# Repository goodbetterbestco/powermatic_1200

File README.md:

# Powermatic 1200 Controls Retrofit

Rev P is the current contactor-based design. Operator controls use 24 VDC; motor-power switching is in the panel enclosure. Schematic, layout and commissioning work remain open.

Backplate layout and DIN-rail/wire-duct installation are complete, as reported on 2026-10-27. All 20 mounting holes were drilled and tapped 10-24; the specified 10-24 fasteners worked well. See the [installation record](docs/WIRING_STANDARD.md#current-document-set---2026-11-09).

Modules and terminal blocks were reported placed on 2026-10-28. The 2026-10-30 saved layout places FH1 at the lower rail’s right end, after 5K, G4 and the existing end stop. Incoming phase blocks 4E/4F/4G are removed; the cable phases now terminate directly at FH1. G4 remains. The mains entry is on the right wall; the two alternate right-face motor/control holes are recorded in the enclosure drawing. Two McMaster 9357K15 gasketed plugs with hex retaining nuts cover the unused motor/control pair. Terminal labels use module number + letter, skipping I/O, with G1-G6 for grounding blocks. Jumper installation is the next assembly step.

## Active files

- [BOM](BOM_other.csv): project requirements and purchasing quantities. `BOM_jlcpcb.csv` is reserved for a separate JLCPCB BOM when needed.
- [KiCad project](kicad/powermatic_1200/powermatic_1200.kicad_pro) and [schematic](kicad/powermatic_1200/powermatic_1200.kicad_sch).

The `docs/` folder contains eight essential files:

- [Panel drawings](docs/Panel_drawings.pdf): module layout, terminal jumpers and markers, approved backpanel drilling sheet, and enclosure holes. The enclosure sheet is PDF page 6; print it at 96% for 1:1 details. The earlier BB1/BB2 busbar artwork is superseded by the six K1/K2 wire jumpers in the wiring guide.
- [Wire installation guide](docs/Wire_installation_guide.pdf): labeling, connector identification and strip settings on PDF pages 2-5, followed by the 131-row installation checklist on pages 6-8.
- [Wiring standard and reference notes](docs/WIRING_STANDARD.md): wiring policy, installation sequence, terminal numbering, signal names, preparation sources, and the two supplemental pendant-jumper records.
- [Saved wire schedule](docs/Wire_schedule.csv): 129 native wires; the printable guide also includes two supplemental pendant jumpers.
- [Wire length totals](docs/Wire_length_totals.csv).
- [Connector inventory](docs/Wire_connector_bins.csv), [installation order](docs/Wire_installation_groups.json), and [termination-code mapping](docs/Wire_termination_types.json): required inputs for Project Review Refresh.

Refresh updates the saved schedule and wire totals. Rebuild and reconcile the PDF guide after changing the native wiring; Refresh does not rebuild it. Preserve the two supplemental pendant rows recorded in the wiring standard.

## Project Review

Double-click **Project Review.app** to launch the separate [bom_review editor](https://github.com/goodbetterbestco/bom_review), installed at `~/Projects/bom_review`. **Documents** lists root CSVs plus the saved wire schedule and wire-length totals in `docs/`. **Overwrite** saves the selected document; **Save file** downloads a copy. For **Wire_schedule.csv**, **Refresh** regenerates the schedule and length totals from saved KiCad; for other documents it reloads the saved CSV. The extractor and project configuration live in `~/Projects/bom_review/adapters/powermatic_1200/`, outside this hardware repository.

`QUA` is the project requirement in pieces or feet. `PACK` is the amount per purchase unit, `ORDER` is the number of purchase units, and `COST` is the price per purchase unit. `LINE = ORDER × COST`. GBB items are on hand and keep `ORDER = 0`. The CSV is manually reviewed; the launcher does not regenerate it from KiCad.

`FLAG` and `FLAG DESCRIPTION` retain the review selection and its document-wide description in the CSV. The app displays them through the checkbox and Description controls. Use **Overwrite** to save changes; reopening or Refresh restores the saved flags. Flags indicate the purpose stated in Description and do not change purchasing quantities.

## Shared parts

Reusable symbols, footprints, models and datasheets belong in the sibling `_parts` repository. The enclosure selection is Hammond EN4SD30208GY with EP3020 backplate. Verify the saved schematic, board and physical fit independently before fabrication or procurement.

## Repository policy

See [AGENTS.md](AGENTS.md). Supporting documents belong in `docs/`; temporary tools, generated reviews and automatic backup folders are removed. Earlier scripts and reports remain available in Git history when previously committed.

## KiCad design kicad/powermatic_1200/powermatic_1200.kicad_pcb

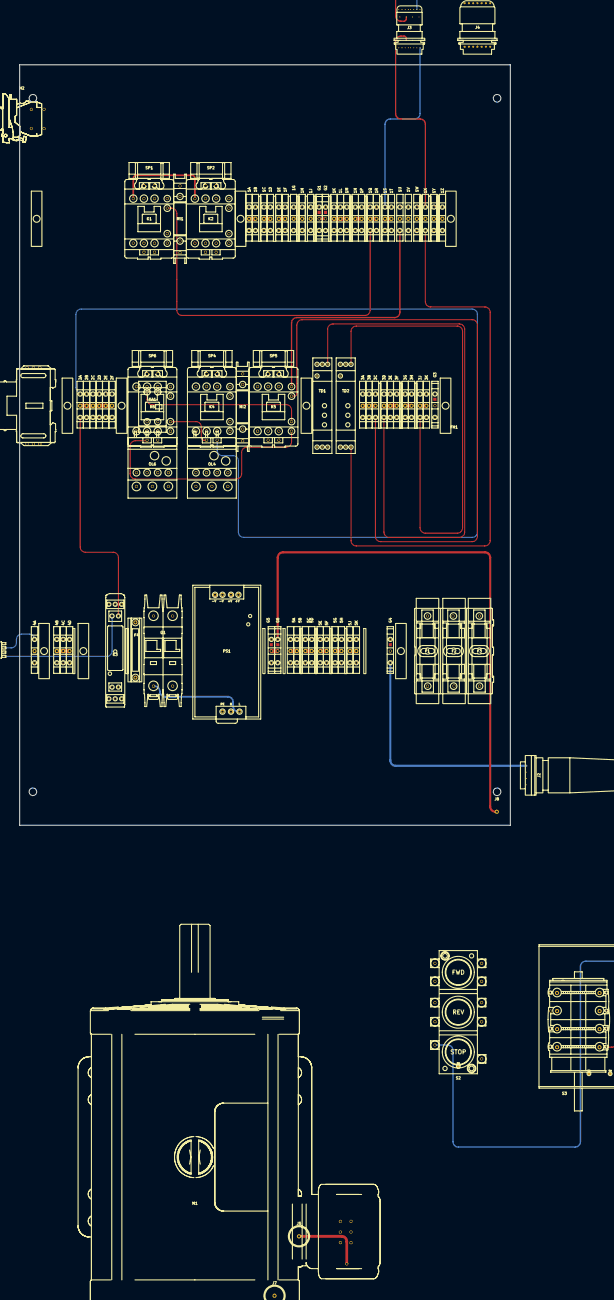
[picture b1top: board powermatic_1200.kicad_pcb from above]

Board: 24 copper layers, 462.0 x 716.0 mm, 105 parts (0 on the bottom side), 55 nets.

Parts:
1A, 1B, 1C, 1D, 1E, 1F, 1G, 1H, 1J, 1K, 1L, 1M, 1N, 1P, 1Q, 1R, 1S, 1T, 1U, 1V, 1W, 1X, 1Y, 1Z, 2A, 2B, 2C, 2D, 2E, 2F, 3A, 3B, 3C, 3D, 3E, 3F, 3G, 3H, 3J, 3K, 4A, 4B, 4C, 4D, 5A, 5B, 5C, 5D, 5E, 5F, 5G, 5H, 5J, 5K: KN-T12GRY-25; KN-T12GRY-25_Front
BP1: EP3020; EP3020_Front
F1, F2, F3: FRN-R-10; FRN-R-10_RM25030-3SR_Front
F4: 281-623; 281-623_Front
FC4: 9553T2; 9553T2_Front
FH1: RM25030-3SR; RM25030-3SR_Front
G1, G2, G3, G4, G5, G6: KN-G12SP-10; KN-G12SP-10_Front
GL1, GL2: WGNDKT; TestPoint_Pad_D3.0mm
GS1: 221-613; TestPoint_Pad_D3.0mm
H1: XB4BVB1; XB4BVB1_LeftWall
H2: XB4BVB4; XB4BVB4_LeftWall
J1: T4171310004-001; T4171310004-001_LeftWall
J2: 3PH-4W-PLUG; BNSPDX-23-W_MainsPlug_BottomWall
J3: BSPBX-22-W; BSPBX-22-W_BottomWall
J4: BSPDX-23-W; BSPDX-23-W_BottomWall
J5, J7, J8: Frame_PE_Lug_20mm
J6: J6; J6_Termination_Metadata
K1, K2, K4, K5, K6: HMC-9B30-11-DS; HMC-9B30-11-DS_Front
K3: HC3096N-52-900-24; HC3096N-52-900-24_Front
KA1: HMX1-AUX11-F; HMX1-AUX11-F_Front
M1: PWRM1200-MOTOR; PWRM1200-MOTOR_Top_150mm
MI1, MI2: HMX1-MI; HMX1-MI_Front
OL4, OL6: HTOR32-6-S; HTOR32-6-S_Front
PS1: NDR-240-24; NDR-240-24_Front
Q1: FAZ-D4/2-NA-L; FAZ-D4-2-NA-L_Front
S1: PWRM1200-ESTOP; S1_Termination_Metadata
S2: 50MA3KLE; 50MA3KLE_Top
S3: 365-TAV2111; 365-TAV2111_Top
SP1, SP2, SP4, SP5, SP6: HMX1-SSVRC-DC; HMX1-SSVRC-DC_Front
SW1: 222102; 222102_LeftWall
TD1, TD2: RK7817-81-61; RK7817-81-61_Front

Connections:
0V: 2A.BOT, 2A.JMP, 2A.TOP, 2B.BOT, 2B.JMP, 2B.TOP, 2C.BOT, 2C.JMP, 2C.TOP, 2D.BOT, 2D.JMP, 2D.TOP, 2E.BOT, 2E.JMP, 2E.TOP, 2F.BOT, 2F.JMP, 2F.TOP, H1.X2 (LAMP_2), H2.X2 (LAMP_2), K1.A2.BOT (A2_BOT), K1.A2.TOP (A2_TOP), K2.A2.BOT (A2_BOT), K2.A2.TOP (A2_TOP), K3.A2 (COIL-), K4.A2.BOT (A2_BOT), K4.A2.TOP (A2_TOP), K5.A2.BOT (A2_BOT), K5.A2.TOP (A2_TOP), K6.A2.BOT (A2_BOT), K6.A2.TOP (A2_TOP), PS1.1_TOP (-V1), PS1.2_TOP (-V2), SP1.2 (SUP_2), SP2.2 (SUP_2), SP4.2 (SUP_2), SP5.2 (SUP_2), SP6.2 (SUP_2), TD1.A2, TD2.A2
+24V: 4B.BOT, 4B.JMP, 4B.TOP, 4C.BOT, 4C.JMP, 4C.TOP, 4D.BOT, 4D.JMP, 4D.TOP, F4.2, H1.X1 (LAMP_1), J1.1, K3.13 (NO1), K3.31 (NC1)
+24V_RAW: F4.1, PS1.3_TOP (+V1), PS1.4_TOP (+V2)
/+24V_EN: K3.24 (NO2), OL4.95 (TRIP_NC_1)
/CONTROL_ESTOP_DISABLED_FB: H2.X1 (LAMP_1), K3.32 (NC1)
/CONTROL_ESTOP_ENABLE: J1.4, K3.A1+ (COIL+)
/CONTROL_K3_CONTACT_LINK: K3.14 (NO1), K3.23 (NO2)
/CONTROL_LOW_OVERLOAD_ENABLE: OL4.96 (TRIP_NC_2), OL6.95 (TRIP_NC_1)
/DIRECTION_FWD_COIL: K1.A1.BOT (A1_BOT), K1.A1.TOP (A1_TOP), K2.32 (AUX_NC_2), SP1.1 (SUP_1)
/DIRECTION_REV_COIL: K1.32 (AUX_NC_2), K2.A1.BOT (A1_BOT), K2.A1.TOP (A1_TOP), SP2.1 (SUP_1)
/HS_SHORT: K5.1 (L1), K5.3 (L2), K5.5 (L3)
/L1_FUSED: FH1.P3.B (P3B), SW1.1 (L1)
/L1_HIGH: K6.2 (T1), OL6.IN1 (L1)
/L1_LOW: K4.2 (T1), OL4.IN1 (L1)
/L1_PSU: PS1.3_BOT (L), Q1.2 (T1)
/L2_FUSED: FH1.P2.B (P2B), SW1.3 (L2)
/L2_HIGH: K6.4 (T2), OL6.IN2 (L2)
/L2_LOW: K4.4 (T2), OL4.IN2 (L2)
/L2_PSU: PS1.2_BOT (N), Q1.4 (T2)
/L3_FUSED: FH1.P1.B (P1B), SW1.5 (L3)
/L3_HIGH: K6.6 (T3), OL6.IN3 (L3)
/L3_LOW: K4.6 (T3), OL4.IN3 (L3)
/L3_SW: K1.5 (L3), K2.5 (L3), SW1.6 (T3)
/LOW_K5_RELEASED: K5.32 (AUX_NC_2), KA1.51
/SPEED_HIGH_COIL: K5.44 (AUX_NO_2), K6.A1.BOT (A1_BOT), K6.A1.TOP (A1_TOP), SP6.1 (SUP_1)
/SPEED_HIGH_SHORTING_COIL: K5.A1.BOT (A1_BOT), K5.A1.TOP (A1_TOP), SP5.1 (SUP_1), TD1.18
/SPEED_LOW_COIL: K4.A1.BOT (A1_BOT), K4.A1.TOP (A1_TOP), K6.32 (AUX_NC_2), SP4.1 (SUP_1)
CONTROL_ESTOP_CONTACT_LINK: 4A.BOT, 4A.JMP, 4A.TOP, J1.2, J1.3
CONTROL_OVERLOAD_ENABLE: 1W.BOT, 1W.JMP, 1W.TOP, J3.5.IN, J3.5.OUT, OL6.96 (TRIP_NC_2), S2.1T (FWD_NC_1), S2.3T (REV_NC_1), S2.5T (STOP_NC_1)
CONTROL_RUN_ENABLE: 1S.BOT, 1S.JMP, 1S.TOP, 1T.BOT, 1T.JMP, 1T.TOP, 3A.BOT, 3A.JMP, 3A.TOP, 3B.BOT, 3B.JMP, 3B.TOP, 3C.BOT, 3C.JMP, 3C.TOP, J3.1.IN, J3.1.OUT, J3.8.IN, J3.8.OUT, K1.43 (AUX_NO_1), K2.43 (AUX_NO_1), K4.31 (AUX_NC_1), K4.43 (AUX_NO_1), K5.31 (AUX_NC_1), K6.43 (AUX_NO_1), S2.6T (STOP_NC_2), S3.2B (HI2_B)
DIRECTION_ENABLE: 1K.BOT, 1K.JMP, 1K.TOP, 1L.BOT, 1L.JMP, 1L.TOP, 1M.BOT, 1M.JMP, 1M.TOP, J3.2.IN, J3.2.OUT, K4.44 (AUX_NO_2), K6.44 (AUX_NO_2), S2.2B (FWD_NO_2), S2.4B (REV_NO_2)
DIRECTION_FWD_CMD: 1N.BOT, 1N.JMP, 1N.TOP, 1P.BOT, 1P.JMP, 1P.TOP, J3.3.IN, J3.3.OUT, K1.44 (AUX_NO_2), K2.31 (AUX_NC_1), S2.1B (FWD_NO_1)
DIRECTION_REV_CMD: 1Q.BOT, 1Q.JMP, 1Q.TOP, 1R.BOT, 1R.JMP, 1R.TOP, J3.4.IN, J3.4.OUT, K1.31 (AUX_NC_1), K2.44 (AUX_NO_2), S2.3B (REV_NO_1)
HIGH_SEQUENCE_ENABLE: 1Y.BOT, 1Y.JMP, 1Y.TOP, 3D.BOT, 3D.JMP, 3D.TOP, 3E.BOT, 3E.JMP, 3E.TOP, 3F.BOT, 3F.JMP, 3F.TOP, J3.10.IN, J3.10.OUT, K4.32 (AUX_NC_2), KA1.63, S3.3B (HI3_B), TD1.15, TD1.A3
HIGH_SEQUENCE_TRIGGER: 1Z.BOT, 1Z.JMP, 1Z.TOP, 3G.BOT, 3G.JMP, 3G.TOP, 3H.BOT, 3H.JMP, 3H.TOP, J3.11.IN, J3.11.OUT, KA1.64, S3.3T (HI3_T), TD1.B1
L1_DIR: 5E.BOT, 5E.JMP, 5E.TOP, 5F.BOT, 5F.JMP, 5F.TOP, K1.2 (T1), K2.6 (T3), K4.1 (L1), K6.1 (L1)
L1_IN: FH1.P3.A (P3A), J2.X (L1)
L1_SW: 5A.BOT, 5A.JMP, 5A.TOP, 5B.BOT, 5B.JMP, 5B.TOP, K1.1 (L1), K2.1 (L1), Q1.1 (L1), SW1.2 (T1)
L2_DIR: 5G.BOT, 5G.JMP, 5G.TOP, 5H.BOT, 5H.JMP, 5H.TOP, K1.4 (T2), K2.4 (T2), K4.3 (L2), K6.3 (L2)
L2_IN: FH1.P2.A (P2A), J2.Y (L2)
L2_SW: 5C.BOT, 5C.JMP, 5C.TOP, 5D.BOT, 5D.JMP, 5D.TOP, K1.3 (L2), K2.3 (L2), Q1.3 (L2), SW1.4 (T2)
L3_DIR: 5J.BOT, 5J.JMP, 5J.TOP, 5K.BOT, 5K.JMP, 5K.TOP, K1.6 (T3), K2.2 (T1), K4.5 (L3), K6.5 (L3)
L3_IN: FH1.P1.A (P1A), J2.Z (L3)
LOW_SEQUENCE_ENABLE: 3J.BOT, 3J.JMP, 3J.TOP, 3K.BOT, 3K.JMP, 3K.TOP, KA1.52, TD2.15, TD2.A3
M1_T1: 1A.BOT, 1A.JMP, 1A.TOP, 1B.BOT, 1B.JMP, 1B.TOP, J4.T1.IN, J4.T1.OUT, K5.2 (T1), M1.T1, OL4.2 (T1)
M1_T2: 1C.BOT, 1C.JMP, 1C.TOP, 1D.BOT, 1D.JMP, 1D.TOP, J4.T2.IN, J4.T2.OUT, K5.4 (T2), M1.T2, OL4.4 (T2)
M1_T3: 1E.BOT, 1E.JMP, 1E.TOP, 1F.BOT, 1F.JMP, 1F.TOP, J4.T3.IN, J4.T3.OUT, K5.6 (T3), M1.T3, OL4.6 (T3)
M1_T4: 1G.BOT, 1G.JMP, 1G.TOP, J4.T4.IN, J4.T4.OUT, M1.T4, OL6.2 (T1)
M1_T5: 1H.BOT, 1H.JMP, 1H.TOP, J4.T5.IN, J4.T5.OUT, M1.T5, OL6.4 (T2)
M1_T6: 1J.BOT, 1J.JMP, 1J.TOP, J4.T6.IN, J4.T6.OUT, M1.T6, OL6.6 (T3)
unnamed: S3.7B (LOW7_B), S3.8B (HI8_B)
PE: G1.1, G1.2, G1.JMP, G1.PE, G2.1, G2.2, G2.JMP, G2.PE, G3.1, G3.2, G3.JMP, G3.PE, G4.1, G4.2, G4.JMP, G4.PE, G5.1, G5.2, G5.JMP, G5.PE, G6.1, G6.2, G6.JMP, G6.PE, GL1.1, GL2.1, GS1.1, J2.G (GND), J3.PE.IN, J3.PE.OUT, J4.PE_IN, J4.PE_OUT, J5.PE, J7.PE, J8.PE, M1.PE, PS1.1_BOT (PE)
SPEED_HIGH_CMD: 1U.BOT, 1U.JMP, 1U.TOP, J3.7.IN, J3.7.OUT, K5.43 (AUX_NO_1), S3.2T (HI2_T)
SPEED_LOW_CMD: 1V.BOT, 1V.JMP, 1V.TOP, J3.6.IN, J3.6.OUT, K6.31 (AUX_NC_1), S3.1T (LOW1_T)
SPEED_LOW_TIMED_ENABLE: 1X.BOT, 1X.JMP, 1X.TOP, J3.9.IN, J3.9.OUT, S3.1B (LOW1_B), TD2.18

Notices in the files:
parts and their libraries:
Bimed BSPDX-23-W; manufacturer CAD bottom-wall projection; centerline 75 mm from Hammond EN4SD20208GY rear exterior.
Mains plug routing proxy at the BNSPDX-23-W gland; four X/Y/Z/G conductor targets at the gland exit, not gland contacts.
